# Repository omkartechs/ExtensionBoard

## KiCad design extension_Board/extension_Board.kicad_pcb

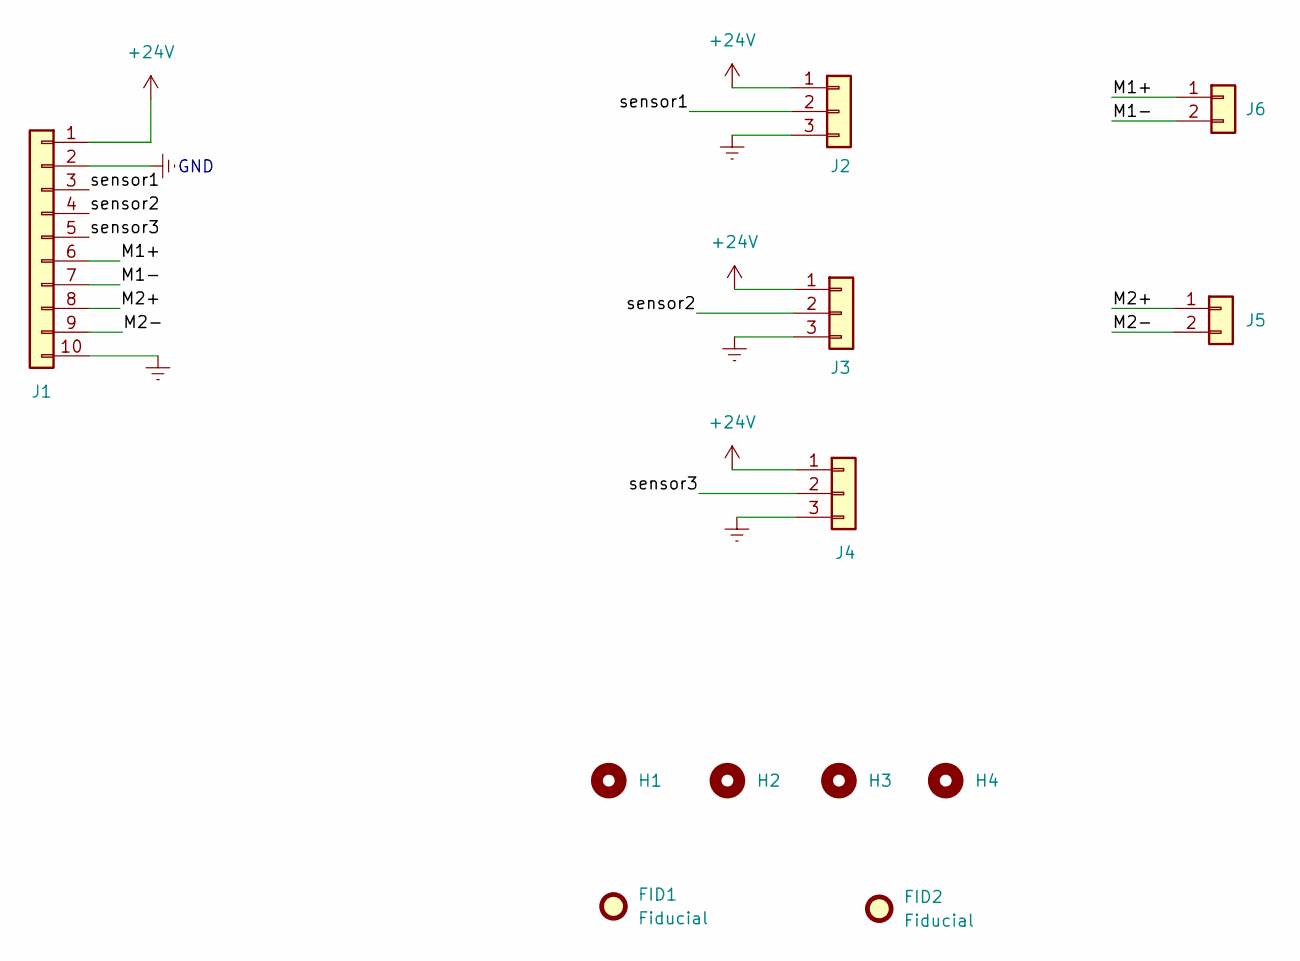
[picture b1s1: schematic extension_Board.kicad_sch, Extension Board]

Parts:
FID1, FID2: Fiducial; Fiducial_0.75mm_Mask1.5mm
H1, H2, H3, H4: MountingHole; MountingHole_3mm_Pad
J1: Conn_01x10; Molex_KK-254_AE-6410-10A_1x10_P2.54mm_Vertical
J2, J3, J4: Conn_01x03; Molex_KK-254_AE-6410-03A_1x03_P2.54mm_Vertical
J5, J6: Conn_01x02; Molex_KK-254_AE-6410-02A_1x02_P2.54mm_Vertical

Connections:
+24V: J1.1, J2.1, J3.1, J4.1
/M1+: J1.6, J6.1
/M1-: J1.7, J6.2
/M2+: J1.8, J5.1
/M2-: J1.9, J5.2
/sensor1: J1.3, J2.2
/sensor2: J1.4, J3.2
/sensor3: J1.5, J4.2
GNDREF: H1.1, H2.1, H3.1, H4.1, J1.2, J1.10, J2.3, J3.3, J4.3

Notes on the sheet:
GND

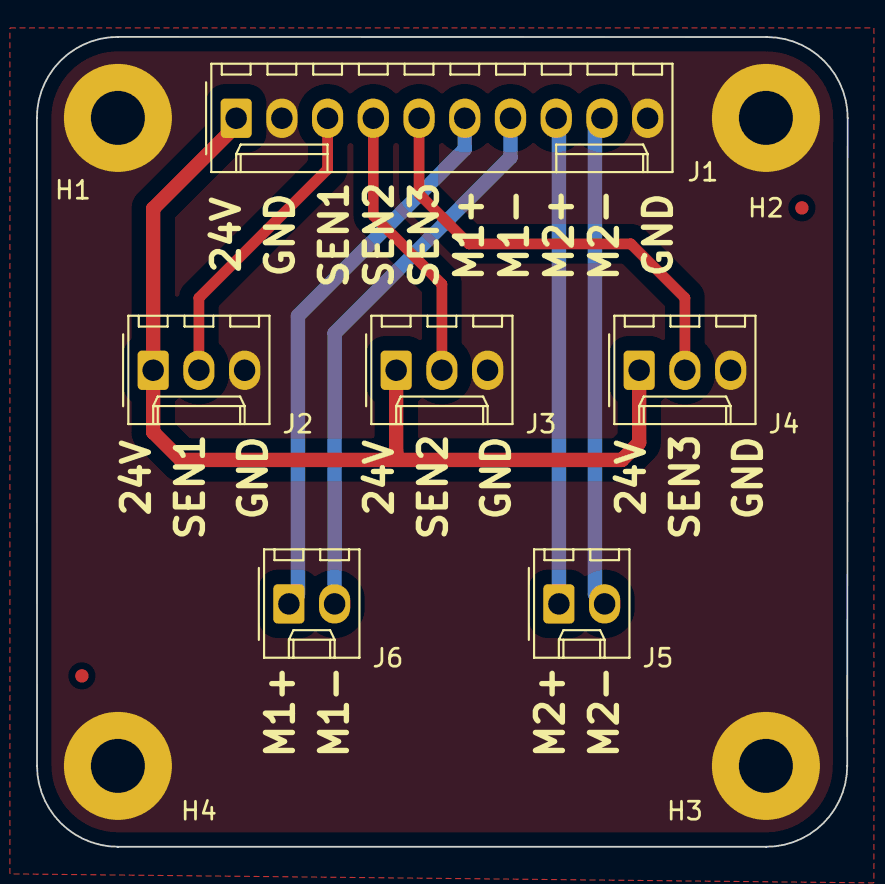
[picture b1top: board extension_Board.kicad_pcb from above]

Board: 2 copper layers, 45.0 x 45.0 mm, 12 parts (0 on the bottom side), 9 nets.

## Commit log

2022-09-27 FILE UPDATE
2022-09-28 gbr file update
